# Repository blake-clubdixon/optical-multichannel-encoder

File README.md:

# optical-multichannel-encoder

## Overview

An experimental optical multi-channel encoding system inspired by the operation of the Enigma Machine (circa 1918).

The project explores transmission, detection, and processing of parallel optical signals through polymer optical fiber (POF) using photodiodes, analog signal conditioning, and digital signal recovery.

## Project Goals

- Develop a 26-channel optical transmission system.
- Investigate optical power loss through the coupling chains.
- Design a photodiode receiver.
- Convert optical signals into electrical signals.
- Integrate the optical, electrical, and mechanical subsystems together.

## System Diagram

*Coming soon*

## Hardware

- 650nm 5mW lasers
- 2mm Polymer optical fiber
- BPW34S photodiode
- MCP602 transimpedance amplifier
- LMV331 comparator
- 2N7000 MOSFET
- 3.7V 1200mAh Battery + Charging Module

## Software & Engineering Tools

- KiCad
- LTspice
- Autodesk Fusion
- Python

## Current Status

The optical receiver module, rotor assembly, power supply board, and lateral displacement couplings have been developed and are in the initial stages of prototyping. 

## Future Work

- Improve coupling efficiency and fiber termination to reduce optical power loss.
- Test and characterize receiver sensitivity.
- Scale single-channel tests to larger multi-channel tests.
- Integrate encoding rotors and pawl mechanisms.
- Design a custom PCB

## Author

Blake Dixon

Electrical Engineering
Texas Tech University

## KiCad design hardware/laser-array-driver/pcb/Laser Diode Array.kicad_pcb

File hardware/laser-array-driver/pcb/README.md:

# PCB

KiCad PCB schematic for the laser driver board.

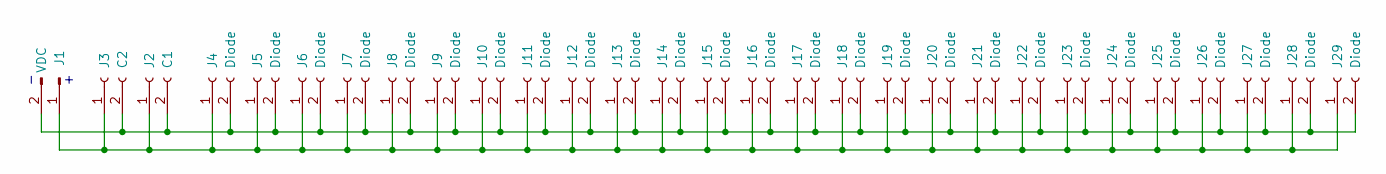
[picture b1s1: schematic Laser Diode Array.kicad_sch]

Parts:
J1: VDC; JST_EH_B2B-EH-A_1x02_P2.50mm_Vertical
J2: C1; CP_Radial_D4.0mm_P2.00mm
J3: C2; CP_Radial_D4.0mm_P2.00mm
J4, J5, J6, J7, J8, J9, J10, J11, J12, J13, J14, J15, J16, J17, J18, J19, J20, J21, J22, J23, J24, J25, J26, J27, J28, J29: Diode; JST_EH_B2B-EH-A_1x02_P2.50mm_Vertical

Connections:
unnamed: J1.1, J2.1, J3.1, J4.1, J5.1, J6.1, J7.1, J8.1, J9.1, J10.1, J11.1, J12.1, J13.1, J14.1, J15.1, J16.1, J17.1, J18.1, J19.1, J20.1, J21.1, J22.1, J23.1, J24.1, J25.1, J26.1, J27.1, J28.1, J29.1
unnamed: J1.2, J2.2, J3.2, J4.2, J5.2, J6.2, J7.2, J8.2, J9.2, J10.2, J11.2, J12.2, J13.2, J14.2, J15.2, J16.2, J17.2, J18.2, J19.2, J20.2, J21.2, J22.2, J23.2, J24.2, J25.2, J26.2, J27.2, J28.2, J29.2

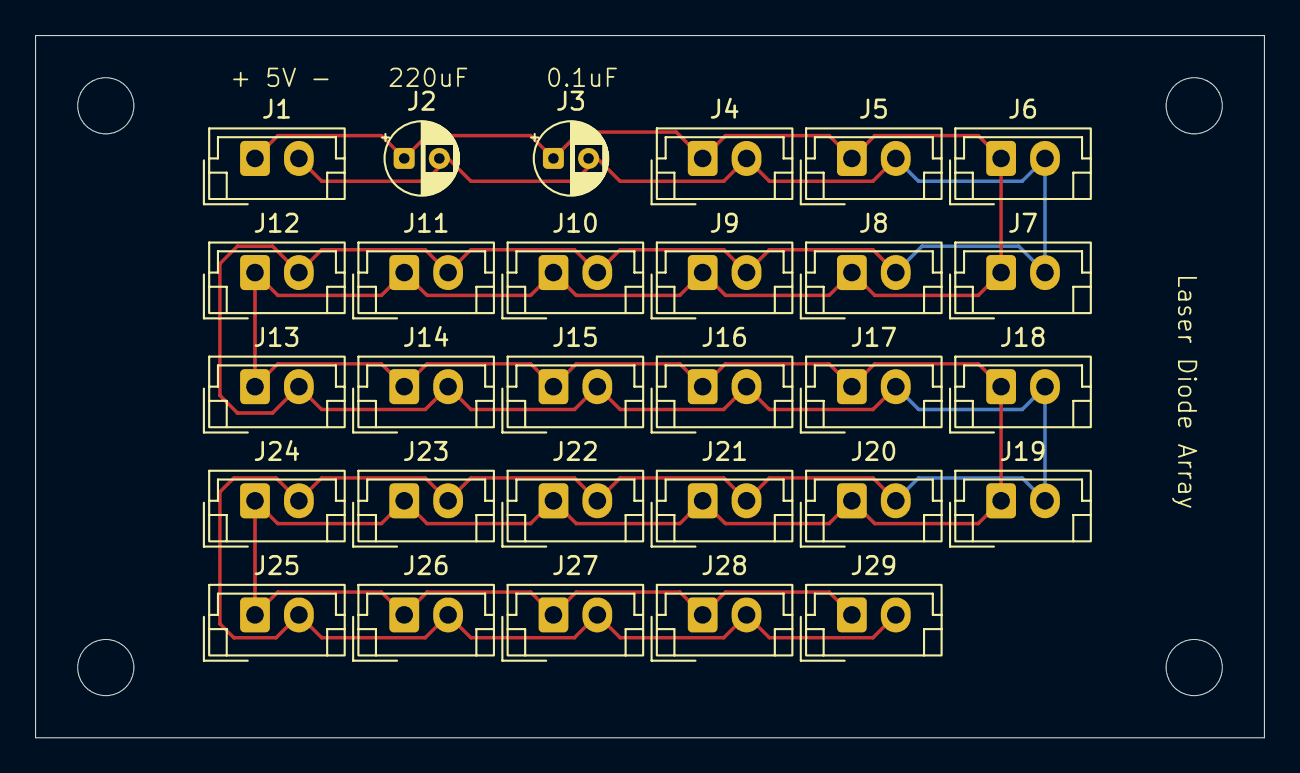
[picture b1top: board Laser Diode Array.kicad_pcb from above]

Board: 2 copper layers, 70.0 x 40.0 mm, 29 parts (0 on the bottom side), 2 nets.
